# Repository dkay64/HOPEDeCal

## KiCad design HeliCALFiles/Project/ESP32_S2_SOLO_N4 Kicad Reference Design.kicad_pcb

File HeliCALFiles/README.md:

# HeliCAL Project

**Authors**  
- Jacob Gottesman  
- Dhruv Kesavarap  
- Myint Shein Hein  

## Overview

This repository contains all design and supporting files for the **HeliCAL Project**, a PCB “hat” for the NVIDIA Jetson Nano that offloads real-time hardware tasks to an ESP32. The primary objective is to enable accurate encoder tracking and reliable PWM control through UART communication, addressing hardware-timer and interrupt limitations on the Jetson Nano.

---

## Project Rationale

### Why Use an ESP32 with a Jetson Nano?
- **Precise Timing**: The Jetson Nano does not provide robust hardware timers for high-speed, deterministic tasks.
- **Reliable Interrupt Handling**: Real-time interrupt-driven tasks like counting encoder ticks or generating precise PWM signals can be offloaded to the ESP32.
- **Efficient I2C/UART Integration**: The ESP32 communicates critical data and signals back to the Jetson Nano over UART or I2C, letting the Nano focus on higher-level tasks such as sensor fusion or machine learning inference.

### System Impact
- This PCB is **crucial** for achieving fine-grained positional control and motion tracking.
- It augments the Jetson Nano by providing dedicated hardware resources, ensuring consistent performance in time-sensitive control loops.

---

## Features

- **ESP32 I2C Slave**: Handles encoders (up to five quadrature encoders), limit switches, and PWM generation.
- **Compact “Hat” Form Factor**: Designed to match the Jetson Nano footprint, stacking headers for direct mounting.
- **External Connections**: 
  - **Limit Switches** (six digital inputs), 
  - **Encoders** (five quadrature interfaces), 
  - **PWM Outputs** (for motor drivers).
- **JST SH Connectors**: Easy plug-and-play for limit switches and encoders.
- **I2C Header**: Standard interface to the Jetson Nano.

---

## Repository Structure

[ADD LATER]

- **Drill Files/**: Contains drill data for PCB fabrication.
- **HeliCALSymbols/**: Custom schematic symbols for KiCad or other EDA tools.
- **Libraries/**: Library files for standard components or footprints.
- **Project/**: Main project files (schematic, PCB layout, settings, etc.).
- **DFM analysis report_JLCDFM_Drill Files.pdf**: Manufacturer’s Design for Manufacturing (DFM) analysis report for the drill files.
- **Drill Files.zip**: Compressed set of all drill files.
- **HeliCAL-Project.zip**: Complete project archive (schematic, layout, BOM).

---

## Getting Started

1. **Clone or Download** this repository.
2. **Unzip** the `HeliCAL-Project.zip` if you plan to open the schematic and PCB layout in your preferred EDA tool (e.g., KiCad).
3. **Install Dependencies** (if needed):
   - [KiCad 9](https://www.kicad.org/) (or whichever EDA tool is used).
   - [ESP-IDF](https://github.com/espressif/esp-idf) or [Arduino Core for ESP32](https://github.com/espressif/arduino-esp32) (for firmware).

4. **Open the Project Files**:
   - Schematic: Within the `Project/` directory (or extracted folder from `HeliCAL-Project.zip`).
   - PCB Layout: Same directory, typically `.kicad_pcb` or equivalent.

---

## Documentation

### 1. Project Overview
- The **Project Overview** and objective can be found in the following [Design Documentation](https://docs.google.com/document/d/1W3Rr75G_mAyZYp311O1N4kCC289wXiKfa5qg6Yp5ShQ/edit?usp=sharing).
- Focuses on enhancing the Jetson Nano’s real-time capabilities using an ESP32 as an I2C/UART slave microcontroller.

### 2. Scope
- Covers the **PCB design**, **fabrication**, and **software implementation** for the ESP32 on the Jetson Nano.
- **Excludes** higher-level software application layers, enclosure designs, and robust thermal management beyond ensuring adequate component ratings.

### 3. PCB Block Diagram
A conceptual **PCB Block Diagram** (NOT YET INCLUDED AS A SEPARATE IMAGE HERE) outlines:
- **Jetson Nano** connections (5V Power, I2C, UART, etc.).
- **ESP32** module for interrupts and real-time control.
- **Connectors** for encoders, limit switches, PWM outputs.

### 4. Design Details
- **Why**: Jetson Nano’s limited interrupt handling and timer features.
- **Where**: The board sits as a hat on the Jetson Nano, powered by 5V from the Nano itself.
- **What**: 
  - Precise PWM generation for DC motor drivers.
  - Encoder inputs captured via dedicated ESP32 hardware timers.
  - I2C OR UART communication for data exchange with the Nano.

### 5. Specifications
- **Voltage**: 5V from Jetson Nano.
- **Current**: Dependent on external loads for motors, sensors, etc. The ESP32 itself draws ~240 mA max, depending on Wi-Fi/Bluetooth usage (though not primary in this design).
- **Encoders**: Up to five channels, quadrature signals.
- **Limit Switches**: Six digital inputs.
- **PWM**: Multiple output channels to drive external motor controllers.

### 6. Design Trade-offs
- **Buck vs. Linear Regulation**: Decided to rely on Jetson Nano’s 5V supply for simplicity and minimal heat generation on-board.
- **Pin Count**: JST SH connectors chosen to save space; trade-off is smaller pitch, requiring careful assembly.

### 7. Bill of Materials (BOM)
- A detailed **BOM** is provided in the `Project/` directory and in the main design files. It includes:
  - ESP32 module
  - JST SH connectors
  - Stacking headers for Jetson Nano
  - Support components (resistors, capacitors, level shifters if needed)

---

## License
This project is released under [MIT License](LICENSE) (or indicate whichever license you prefer). Please see the `LICENSE` file for more details.

---

## References & Appendices
- **Datasheets**:  
  - [ESP32](https://www.espressif.com/en/products/socs/esp32)
  - [INSERT MPU AND OTHER RELEVANT DATASHEETS]
  - Relevant JST SH connector datasheets
- **Design Files**:  
  - Schematic & PCB layout in `Project/` and `HeliCAL-Project.zip`.
- **Testing Logs**:  
  - See `DFM analysis report_JLCDFM_Drill Files.pdf` for manufacturer feedback.

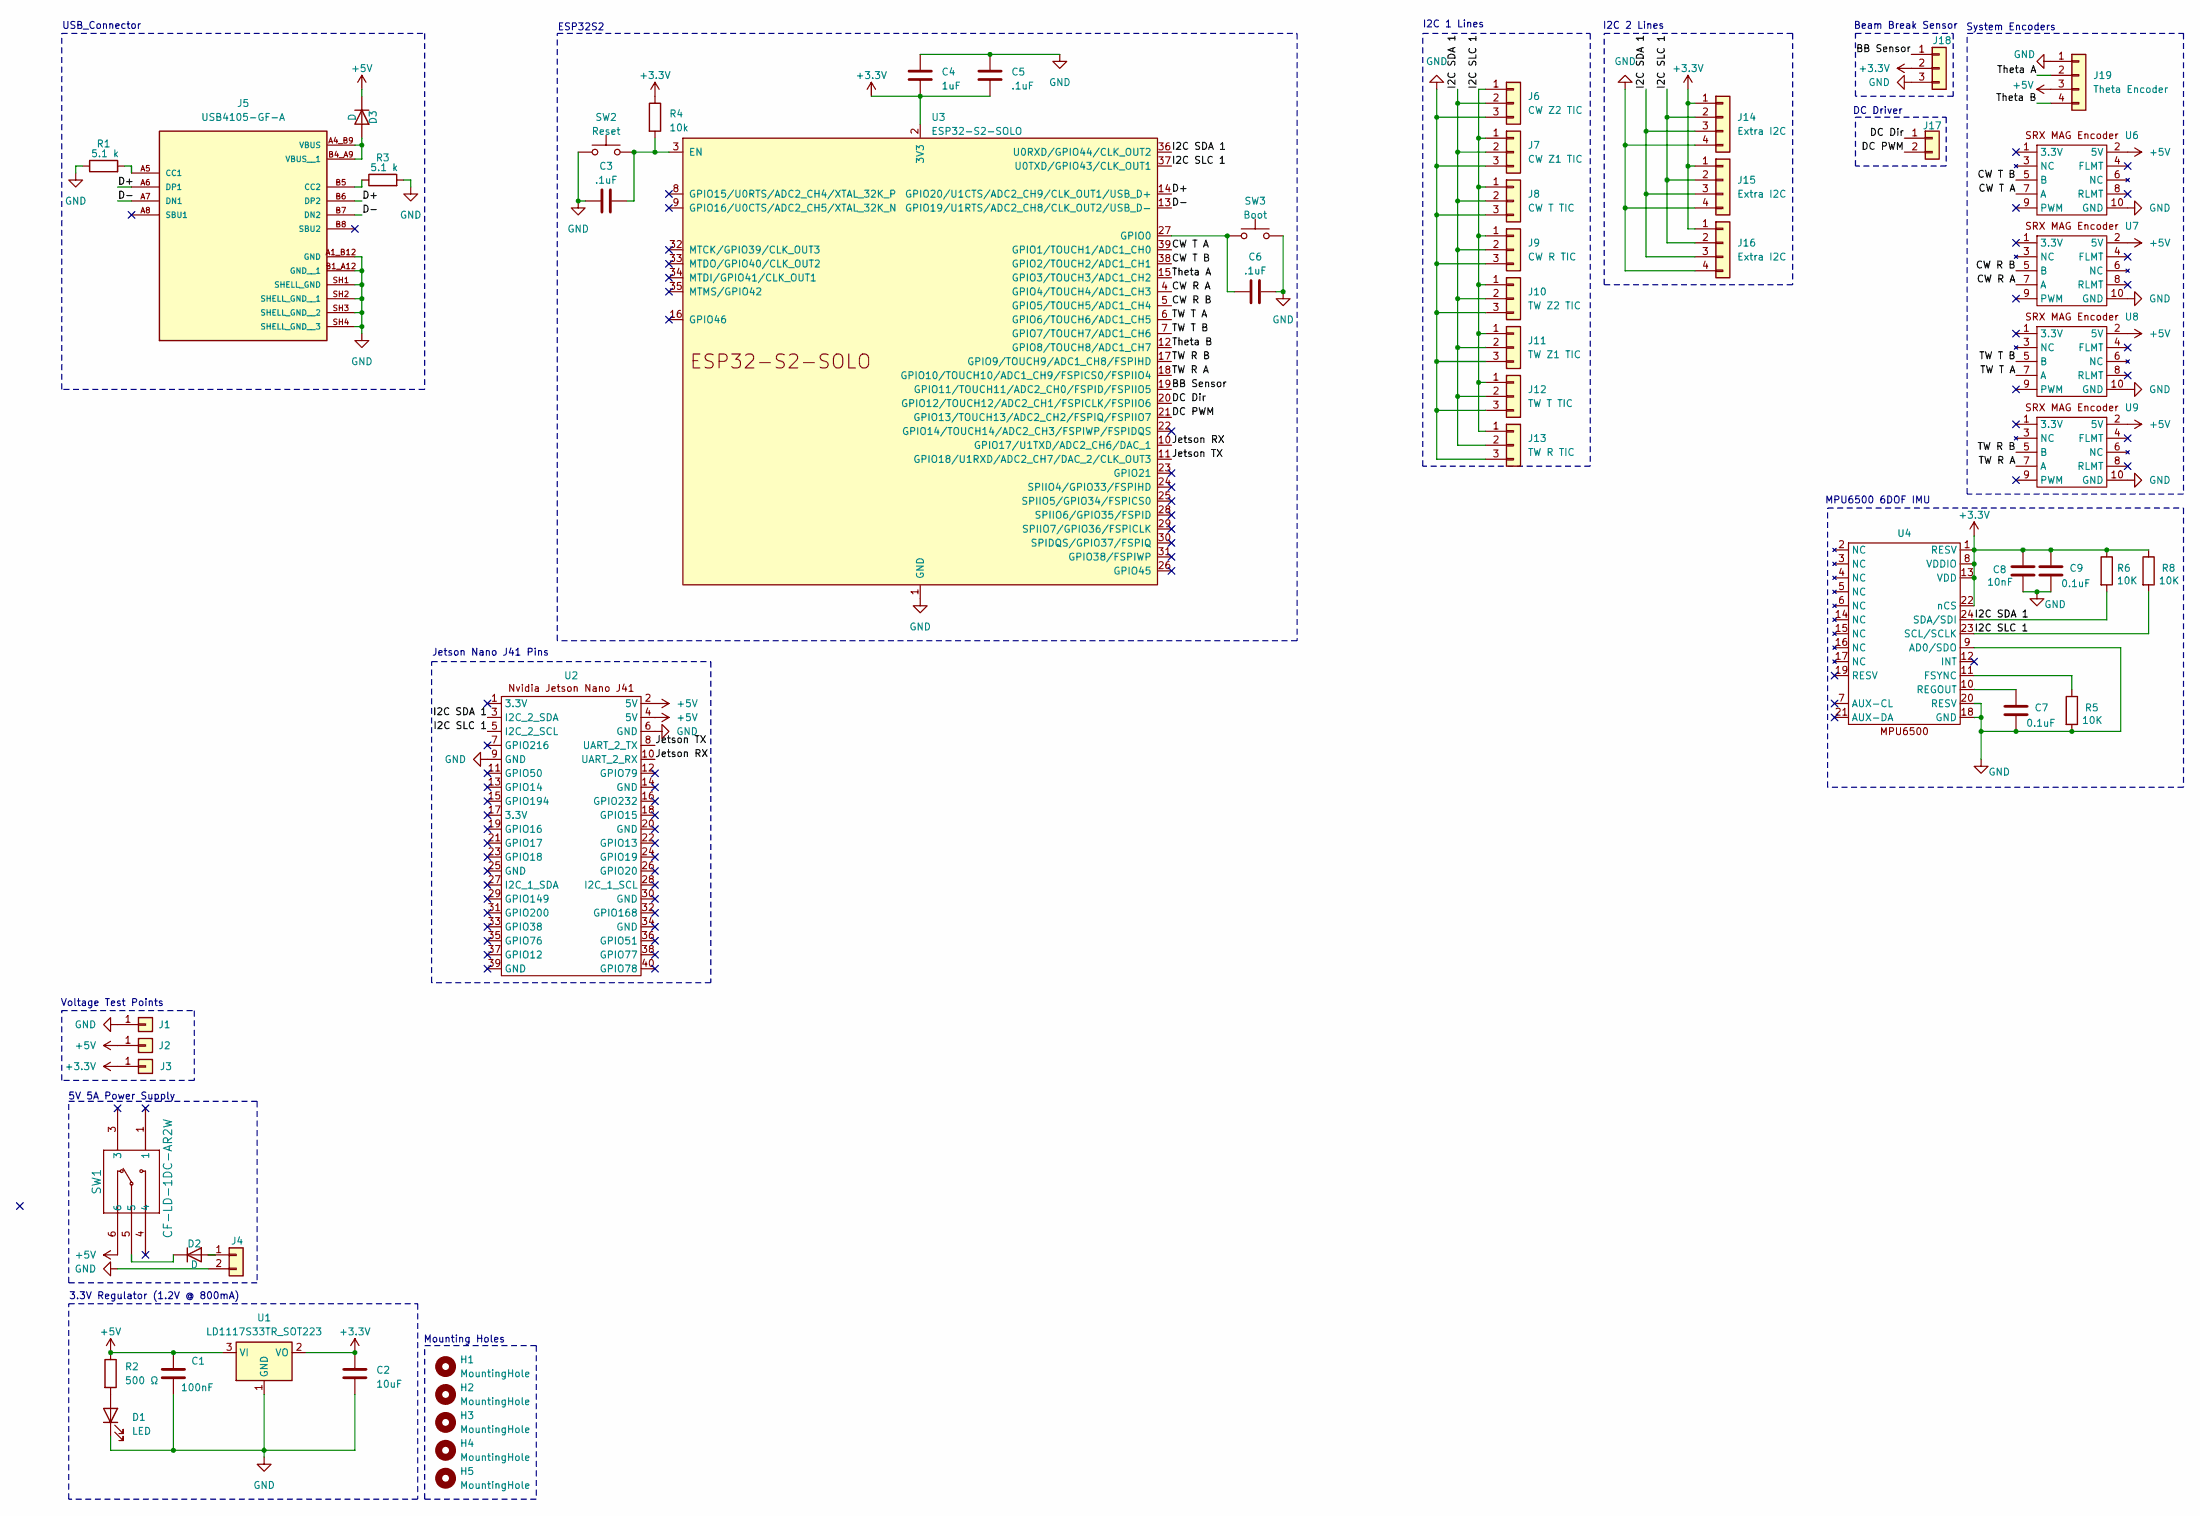
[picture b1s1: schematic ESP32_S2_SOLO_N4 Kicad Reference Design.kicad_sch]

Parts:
C1: 100nF; C_0805_2012Metric
C2: 10uF; C_0603_1608Metric
C3, C5, C6: .1uF; C_0805_2012Metric
C4: 1uF; C_0805_2012Metric
C7, C9: 0.1uF; C_0805_2012Metric
C8: 10nF; C_1206_3216Metric
D1: LED; LED_0603_1608Metric
D2, D3: D; D_SMB-SMC_Universal_Handsoldering
H1, H2: MountingHole; MountingHole_2.7mm_Pad_Via
H3, H4, H5: MountingHole; MountingHole_2.5mm_Pad_Via
J1, J2, J3: Conn_01x01; PinSocket_1x01_P2.54mm_Vertical
J4, J17: Conn_01x02; JST_EH_B2B-EH-A_1x02_P2.50mm_Vertical
J5: USB4105-GF-A; GCT_USB4105-GF-A; PARTREV B4
J6: CW Z2 TIC; JST_EH_B3B-EH-A_1x03_P2.50mm_Vertical
J7: CW Z1 TIC; JST_EH_B3B-EH-A_1x03_P2.50mm_Vertical
J8: CW T TIC; JST_EH_B3B-EH-A_1x03_P2.50mm_Vertical
J9: CW R TIC; JST_EH_B3B-EH-A_1x03_P2.50mm_Vertical
J10: TW Z2 TIC; JST_EH_B3B-EH-A_1x03_P2.50mm_Vertical
J11: TW Z1 TIC; JST_EH_B3B-EH-A_1x03_P2.50mm_Vertical
J12: TW T TIC; JST_EH_B3B-EH-A_1x03_P2.50mm_Vertical
J13: TW R TIC; JST_EH_B3B-EH-A_1x03_P2.50mm_Vertical
J14, J15, J16: Extra I2C; JST_EH_B4B-EH-A_1x04_P2.50mm_Vertical
J18: Conn_01x03; JST_EH_B3B-EH-A_1x03_P2.50mm_Vertical
J19: Theta Encoder; JST_EH_B4B-EH-A_1x04_P2.50mm_Vertical
R1, R3: 5.1 k; R_0603_1608Metric
R2: 500 Ω; R_0603_1608Metric
R4: 10k; R_0805_2012Metric
R5, R6, R8: 10K; R_0805_2012Metric
SW1: CF-LD-1DC-AR2W; CF-LD-1DC-AR2W_NDC
SW2: Reset; TE_4-1437565-9
SW3: Boot; TE_4-1437565-9
U1: LD1117S33TR_SOT223; SOT-223-3_TabPin2
U2: PinHeader_2x20_P2.54mm_Vertical
U3: ESP32-S2-SOLO
U4: InvenSense_QFN-24_3x3mm_P0.4mm
U6, U7, U8, U9: PinHeader_2x05_P1.27mm_Vertical

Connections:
+3.3V: C2.1, C4.2, C5.2, C8.1, C9.1, J3.1, J14.1, J15.1, J16.1, J18.2, R4.1, R6.1, R8.1, U1.2 (VO), U3.2 (3V3), U4.1 (RESV), U4.8 (VDDIO), U4.13 (VDD), U4.22 (nCS)
+5V: C1.1, D3.1 (K), J2.1, J19.3, R2.1, SW1.6, U1.3 (VI), U2.2 (5V), U2.4 (5V), U6.2 (5V), U7.2 (5V), U8.2 (5V), U9.2 (5V)
/BB Sensor: J18.1, U3.19 (GPIO11/TOUCH11/ADC2_CH0/FSPID/FSPIIO5)
/CW R A: U3.4 (GPIO4/TOUCH4/ADC1_CH3), U7.7 (A)
/CW R B: U3.5 (GPIO5/TOUCH5/ADC1_CH4), U7.5 (B)
/CW T A: U3.39 (GPIO1/TOUCH1/ADC1_CH0), U6.7 (A)
/CW T B: U3.38 (GPIO2/TOUCH2/ADC1_CH1), U6.5 (B)
/D+: J5.A6 (DP1), J5.B6 (DP2), U3.14 (GPIO20/U1CTS/ADC2_CH9/CLK_OUT1/USB_D+)
/D-: J5.A7 (DN1), J5.B7 (DN2), U3.13 (GPIO19/U1RTS/ADC2_CH8/CLK_OUT2/USB_D-)
/DC Dir: J17.1, U3.20 (GPIO12/TOUCH12/ADC2_CH1/FSPICLK/FSPIIO6)
/DC PWM: J17.2, U3.21 (GPIO13/TOUCH13/ADC2_CH2/FSPIQ/FSPIIO7)
/I2C SDA 1: J6.2, J7.2, J8.2, J9.2, J10.2, J11.2, J12.2, J13.2, J14.3, J15.3, J16.3, R6.2, U2.3 (I2C_2_SDA), U3.36 (U0RXD/GPIO44/CLK_OUT2), U4.24 (SDA/SDI)
/I2C SLC 1: J6.1, J7.1, J8.1, J9.1, J10.1, J11.1, J12.1, J13.1, J14.2, J15.2, J16.2, R8.2, U2.5 (I2C_2_SCL), U3.37 (U0TXD/GPIO43/CLK_OUT1), U4.23 (SCL/SCLK)
/Jetson RX: U2.10 (UART_2_RX), U3.10 (GPIO17/U1TXD/ADC2_CH6/DAC_1)
/Jetson TX: U2.8 (UART_2_TX), U3.11 (GPIO18/U1RXD/ADC2_CH7/DAC_2/CLK_OUT3)
/TW R A: U3.18 (GPIO10/TOUCH10/ADC1_CH9/FSPICS0/FSPIIO4), U9.7 (A)
/TW R B: U3.17 (GPIO9/TOUCH9/ADC1_CH8/FSPIHD), U9.5 (B)
/TW T A: U3.6 (GPIO6/TOUCH6/ADC1_CH5), U8.7 (A)
/TW T B: U3.7 (GPIO7/TOUCH7/ADC1_CH6), U8.5 (B)
/Theta A: J19.2, U3.15 (GPIO3/TOUCH3/ADC1_CH2)
/Theta B: J19.4, U3.12 (GPIO8/TOUCH8/ADC1_CH7)
GND: C1.2, C2.2, C3.1, C4.1, C5.1, C6.2, C7.2, C8.2, C9.2, D1.1 (K), J1.1, J4.2, J5.A1_B12 (GND), J5.B1_A12 (GND__1), J5.SH1 (SHELL_GND), J5.SH2 (SHELL_GND__1), J5.SH3 (SHELL_GND__2), J5.SH4 (SHELL_GND__3), J6.3, J7.3, J8.3, J9.3, J10.3, J11.3, J12.3, J13.3, J14.4, J15.4, J16.4, J18.3, J19.1, R1.1, R3.2, R5.2, SW2.1, SW3.2, U1.1 (GND), U2.6 (GND), U2.9 (GND), U3.1 (GND), U3.40 (GND), U3.41 (GND), U4.9 (AD0/SDO), U4.18 (GND), U4.20 (RESV), U6.10 (GND), U7.10 (GND), U8.10 (GND), U9.10 (GND)
unnamed: D1.2 (A), R2.2
unnamed: D2.2 (A), J4.1
unnamed: D2.1 (K), SW1.5
unnamed: D3.2 (A), J5.A4_B9 (VBUS), J5.B4_A9 (VBUS__1)
unnamed: J5.A5 (CC1), R1.2
unnamed: J5.B5 (CC2), R3.1
unnamed: C3.2, R4.2, SW2.2, U3.3 (EN)
unnamed: C6.1, SW3.1, U3.27 (GPIO0)
unnamed: R5.1, U4.11 (FSYNC)
unnamed: C7.1, U4.10 (REGOUT)

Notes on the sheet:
Beam Break Sensor
DC Driver
I2C 1 Lines
MPU6500 6DOF IMU
5V 5A Power Supply
Jetson Nano J41 Pins
Voltage Test Points
Mounting Holes
System Encoders
USB_Connector
ESP32S2
3.3V Regulator (1.2V @ 800mA)
I2C 2 Lines

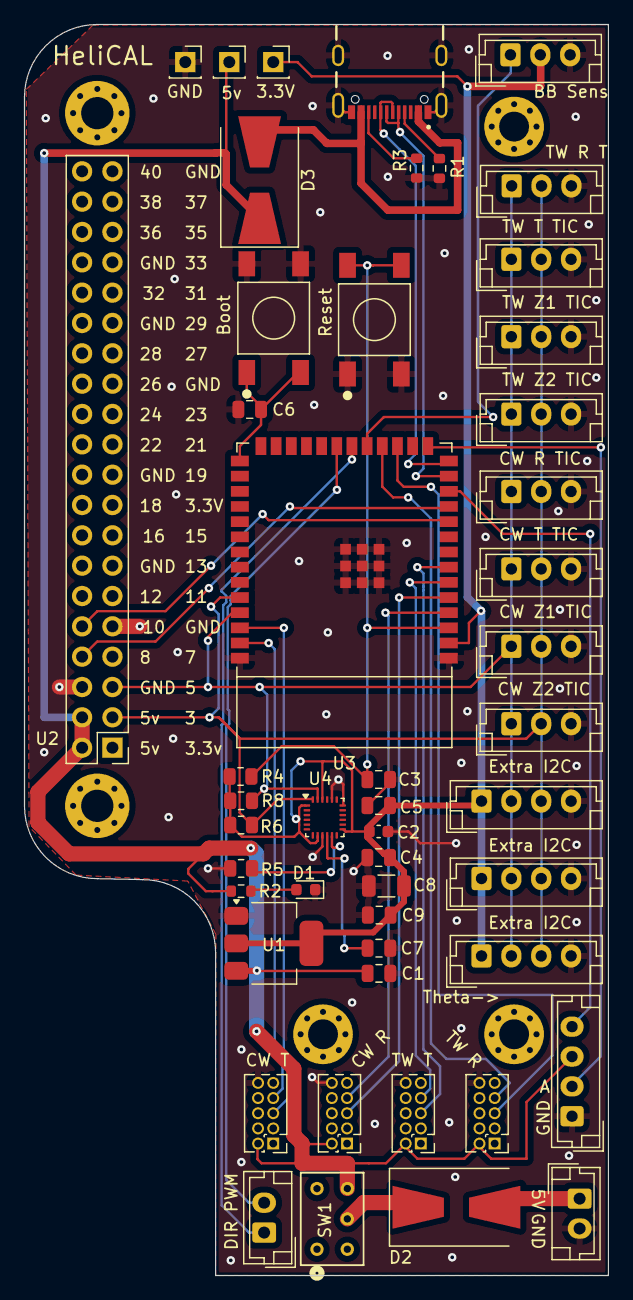
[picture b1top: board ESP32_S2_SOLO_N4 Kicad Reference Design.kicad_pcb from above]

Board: 2 copper layers, 48.9 x 104.7 mm, 54 parts (0 on the bottom side), 32 nets.

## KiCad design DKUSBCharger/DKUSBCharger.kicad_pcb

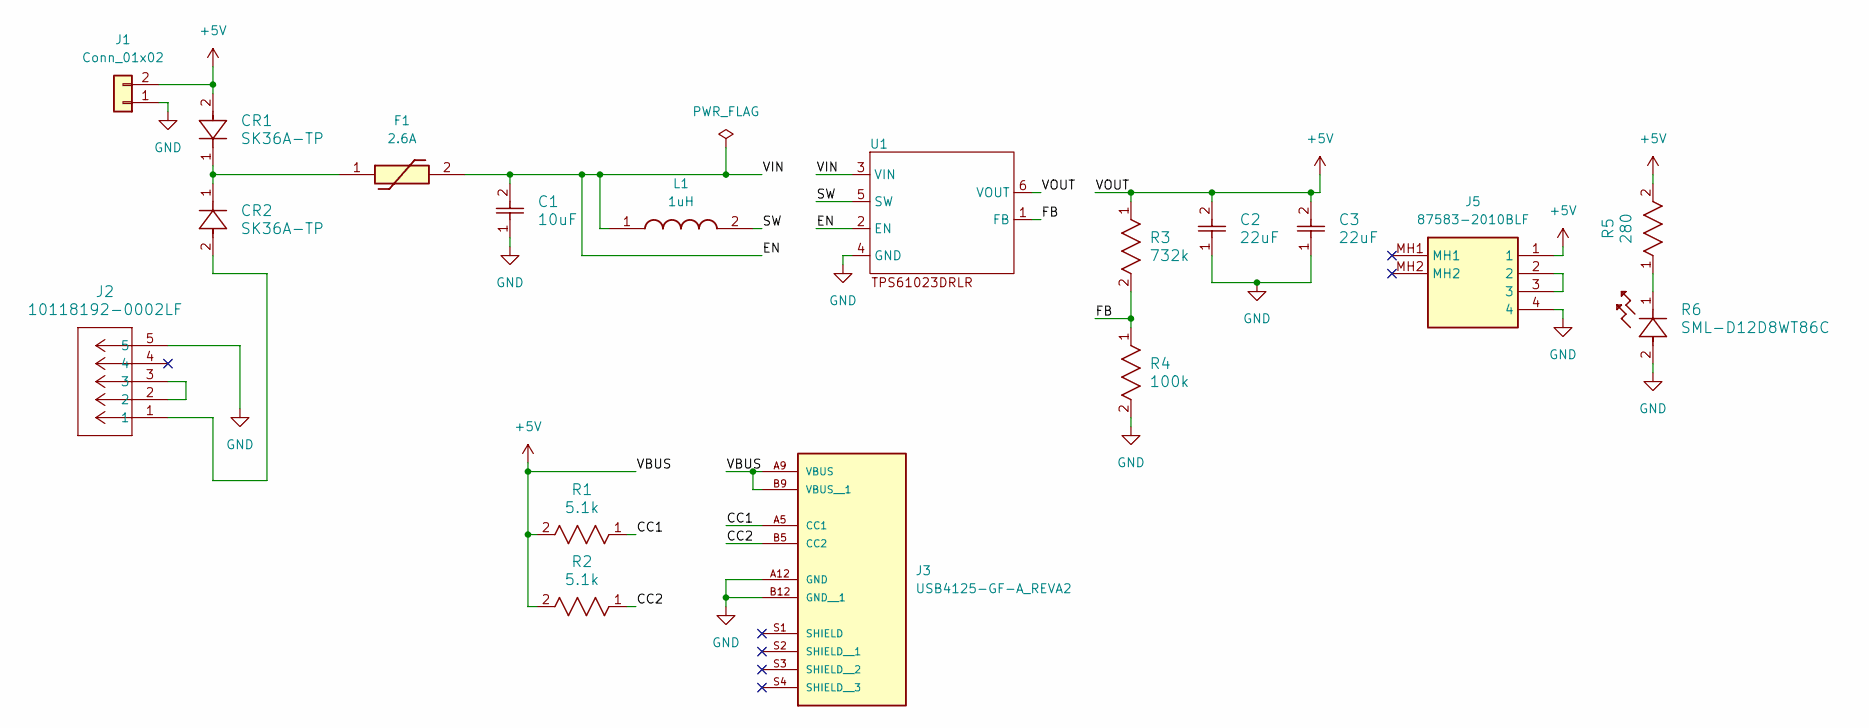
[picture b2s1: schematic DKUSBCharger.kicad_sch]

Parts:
C1: 10uF; CAP_CL10_SAM
C2, C3: 22uF; G-188_MUR
CR1, CR2: SK36A-TP; SMCDO-214AB_MCC
F1: 2.6A; FUSC4632X205N; Manufacturer_Part_Number SMD1812B260TF/12; Mouser Part Number 603-SMD1812B260TF/12
J1: Conn_01x02; PinHeader_1x02_P2.54mm_Vertical
J2: 10118192-0002LF; CONN_10118192-0002LF_AMP
J3: USB4125-GF-A_REVA2; GCT_USB4125-GF-A_REVA2; PARTREV Rev A2
J5: 87583-2010BLF; 875832010BLF; Manufacturer_Part_Number 87583-2010BLF
L1: 1uH; INDC2012X80N; Manufacturer_Part_Number LPWI201208S1R0T; Mouser Part Number 576-LPWI201208S1R0T
R1, R2: 5.1k; RC0603N_YAG
R3: 732k; RC0603N_PAN
R4: 100k; RC0603N_PAN_100k
R5: 280; RESC1608X50N
R6: SML-D12D8WT86C; LED_SMLD12_ROM
U1: DRL0006A

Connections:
+5V: C2.2, C3.2, CR1.2, J1.2, J3.A9 (VBUS), J3.B9 (VBUS__1), J5.1, R1.2, R2.2, R3.1, R5.2, U1.6 (VOUT)
/CC1: J3.A5 (CC1), R1.1
/CC2: J3.B5 (CC2), R2.1
/EN: C1.2, F1.2, L1.1, U1.2 (EN), U1.3 (VIN)
/FB: R3.2, R4.1, U1.1 (FB)
/SW: L1.2, U1.5 (SW)
GND: C1.1, C2.1, C3.1, J1.1, J2.5, J3.A12 (GND), J3.B12 (GND__1), J5.4, R4.2, R6.2, U1.4 (GND)
unnamed: CR1.1, CR2.1, F1.1
unnamed: CR2.2, J2.1
unnamed: J2.2, J2.3
unnamed: J5.2, J5.3
unnamed: R5.1, R6.1

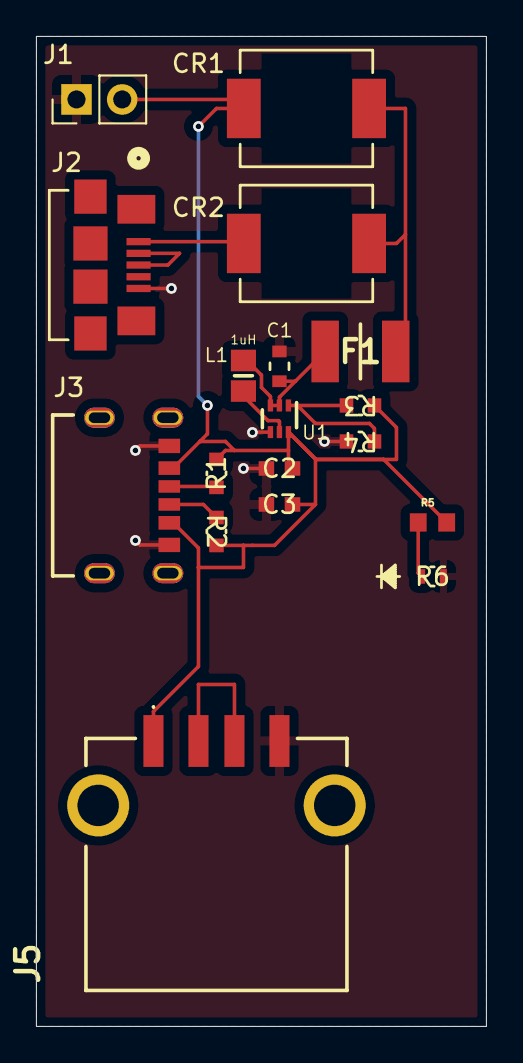
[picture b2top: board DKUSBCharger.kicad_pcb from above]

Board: 2 copper layers, 25.0 x 55.0 mm, 18 parts (0 on the bottom side), 12 nets.

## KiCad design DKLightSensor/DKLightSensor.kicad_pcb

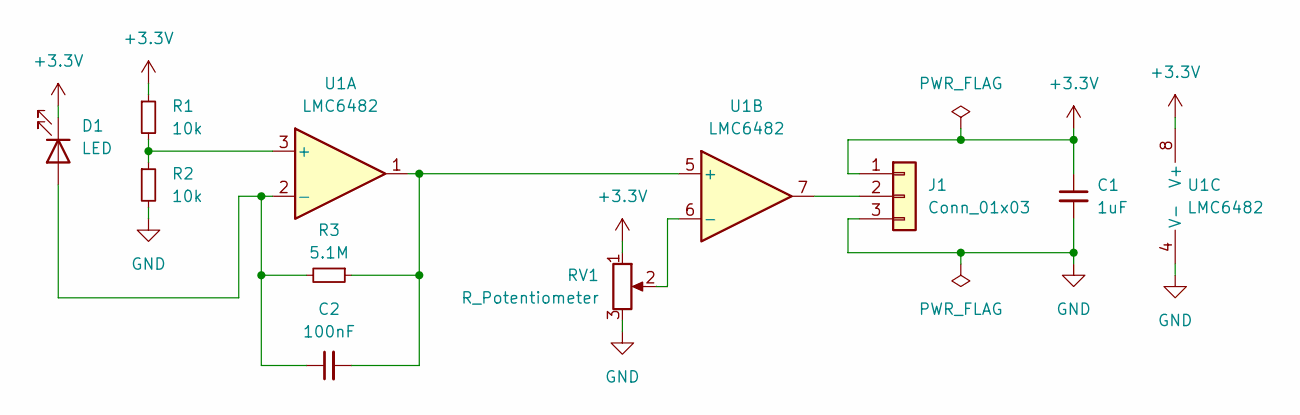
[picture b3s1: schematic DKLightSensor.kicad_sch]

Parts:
C1: 1uF; C_0805_2012Metric
C2: 100nF; C_0805_2012Metric
D1: LED; LED_D5.0mm
J1: Conn_01x03; PinHeader_1x03_P2.54mm_Vertical
R1, R2: 10k; R_Axial_DIN0204_L3.6mm_D1.6mm_P5.08mm_Horizontal
R3: 5.1M; R_Axial_DIN0204_L3.6mm_D1.6mm_P5.08mm_Horizontal
RV1: R_Potentiometer; Potentiometer_Vishay_T7-YA_Single_Vertical
U1: LMC6482; DIP-8_W7.62mm

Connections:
+3.3V: C1.1, D1.1 (K), J1.1, R1.1, RV1.1, U1.8 (V+)
GND: C1.2, J1.3, R2.2, RV1.3, U1.4 (V-)
unnamed: C2.1, D1.2 (A), R3.2, U1.2 (-)
unnamed: J1.2, U1.7
unnamed: R1.2, R2.1, U1.3 (+)
unnamed: C2.2, R3.1, U1.1, U1.5 (+)
unnamed: RV1.2, U1.6 (-)

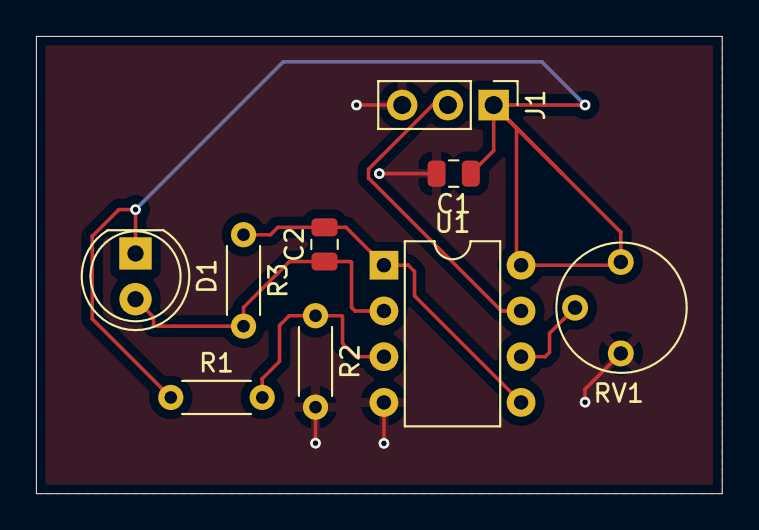
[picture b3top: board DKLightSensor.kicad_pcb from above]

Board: 2 copper layers, 38.1 x 25.4 mm, 9 parts (0 on the bottom side), 7 nets.

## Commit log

2025-01-30 1/29/2025 test push
2025-02-07 Assigned footprints (floorplanning pending)
2025-02-07 Continued layout
2025-02-08 Changed connector placement
2025-02-08 minimized daisy-chaining (tried to route directly from input power source)
2025-02-14 deleted trace between diode and resistor
2025-02-27 Created new proj USBCharger
2025-02-28 added 4 components; created symbol
2025-02-28 added fuse and schottky diode
2025-02-28 finished usb charger schematic
2025-02-28 Schematic
2025-02-28 Fixing schematic symbols
2025-02-28 Assigning footprints in schematic
2025-02-28 finished assigning footprints; updated PCB
2025-03-01 continuing footprint assignmnets
2025-03-05 Continuing annotations
2025-03-06 Created dedicated Footprints and Symbols folders
2025-03-06 Finished assigning footprints
2025-03-06 Fixed footprints
2025-03-06 Fixed footprints; started PCB floorplanning
2025-03-06 Finished PCB
2025-03-06 Fixing DRC errors
2025-03-09 Post check-off edits
2025-05-08 added helical files
